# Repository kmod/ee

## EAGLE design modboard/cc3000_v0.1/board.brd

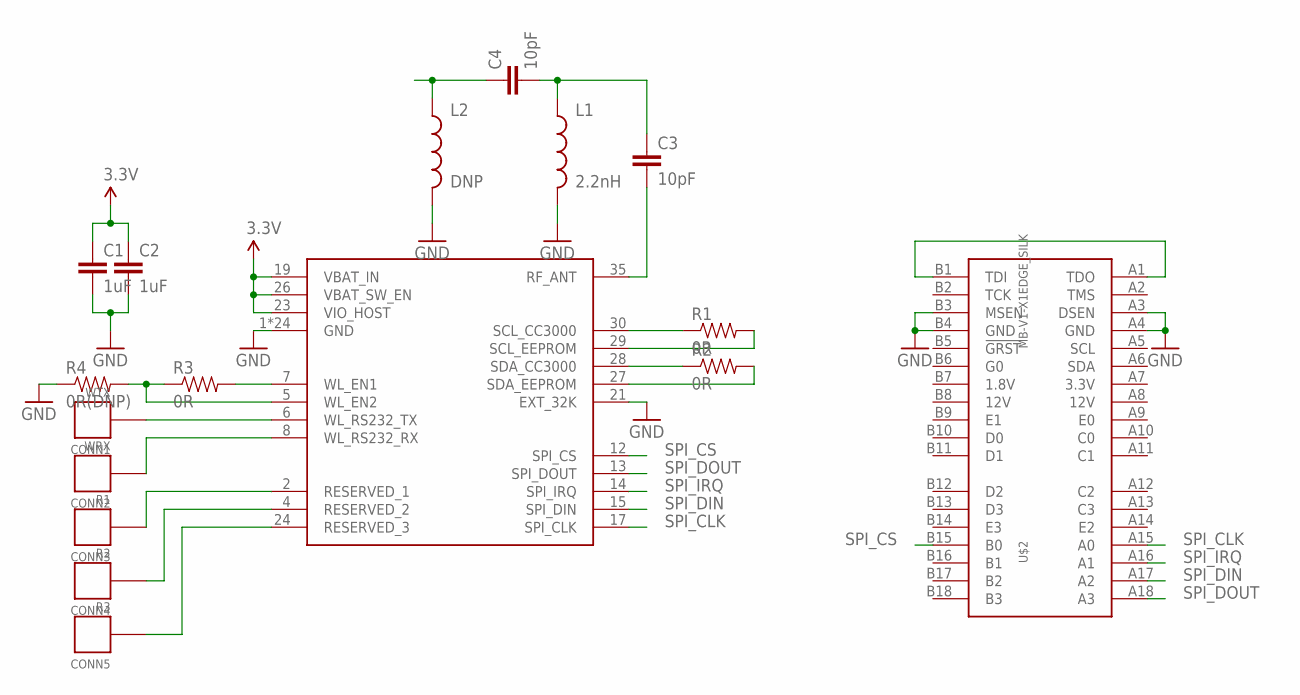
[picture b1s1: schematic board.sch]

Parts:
C1, C2: 1uF; 0603-CAP
C3, C4: 10pF; 0402-CAP
CONN1: WTX; HOLE_22AWG
CONN2: WRX; HOLE_22AWG
CONN3: R1; HOLE_22AWG
CONN4: R2; HOLE_22AWG
CONN5: R3; HOLE_22AWG
L1: 2.2nH; 0603
L2: DNP; 0603
R1, R2, R3: 0R; 0603-RES
R4: 0R(DNP); 0603-RES
U$1: CC3000
U$2: MB-V1-X1EDGE_SILK; MB-V1-X1-EDGE

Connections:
3.3V: C1.1, C2.1, U$1.19 (VBAT_IN), U$1.23 (VIO_HOST), U$1.26 (VBAT_SW_EN)
GND: C1.2, C2.2, L1.2, L2.2, R4.1, U$1.1 (GND), U$1.9 (GND), U$1.10 (GND), U$1.11 (GND), U$1.16 (GND), U$1.18 (GND), U$1.20 (GND), U$1.21 (EXT_32K), U$1.22 (GND), U$1.25 (GND), U$1.31 (GND), U$1.32 (GND), U$1.33 (GND), U$1.34 (GND), U$1.36 (GND), U$1.37 (GND), U$1.38 (GND), U$1.39 (GND), U$1.40 (GND), U$1.41 (GND), U$1.42 (GND), U$1.43 (GND), U$1.44 (GND), U$1.45 (GND), U$1.46 (GND), U$2.A3 (DSEN), U$2.A4 (GND), U$2.B3 (MSEN), U$2.B4 (GND)
unnamed: R1.1, U$1.30 (SCL_CC3000)
unnamed: R1.2, U$1.29 (SCL_EEPROM)
unnamed: R2.1, U$1.28 (SDA_CC3000)
unnamed: R2.2, U$1.27 (SDA_EEPROM)
unnamed: R3.2, U$1.7 (WL_EN1)
unnamed: R3.1, R4.2, U$1.5 (WL_EN2)
unnamed: CONN1.P, U$1.6 (WL_RS232_TX)
unnamed: CONN2.P, U$1.8 (WL_RS232_RX)
unnamed: CONN3.P, U$1.2 (RESERVED_1)
unnamed: CONN4.P, U$1.4 (RESERVED_2)
unnamed: CONN5.P, U$1.24 (RESERVED_3)
unnamed: C3.2, U$1.35 (RF_ANT)
unnamed: C3.1, C4.2, L1.1
unnamed: U$2.A1 (TDO), U$2.B1 (TDI)
unnamed: C4.1, L2.1
SPI_CLK: U$1.17 (SPI_CLK), U$2.A15 (A0)
SPI_CS: U$1.12 (SPI_CS), U$2.B15 (B0)
SPI_DIN: U$1.15 (SPI_DIN), U$2.A17 (A2)
SPI_DOUT: U$1.13 (SPI_DOUT), U$2.A18 (A3)
SPI_IRQ: U$1.14 (SPI_IRQ), U$2.A16 (A1)

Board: 2 copper layers, 17 parts (0 on the bottom side), 22 nets, no tracks yet.

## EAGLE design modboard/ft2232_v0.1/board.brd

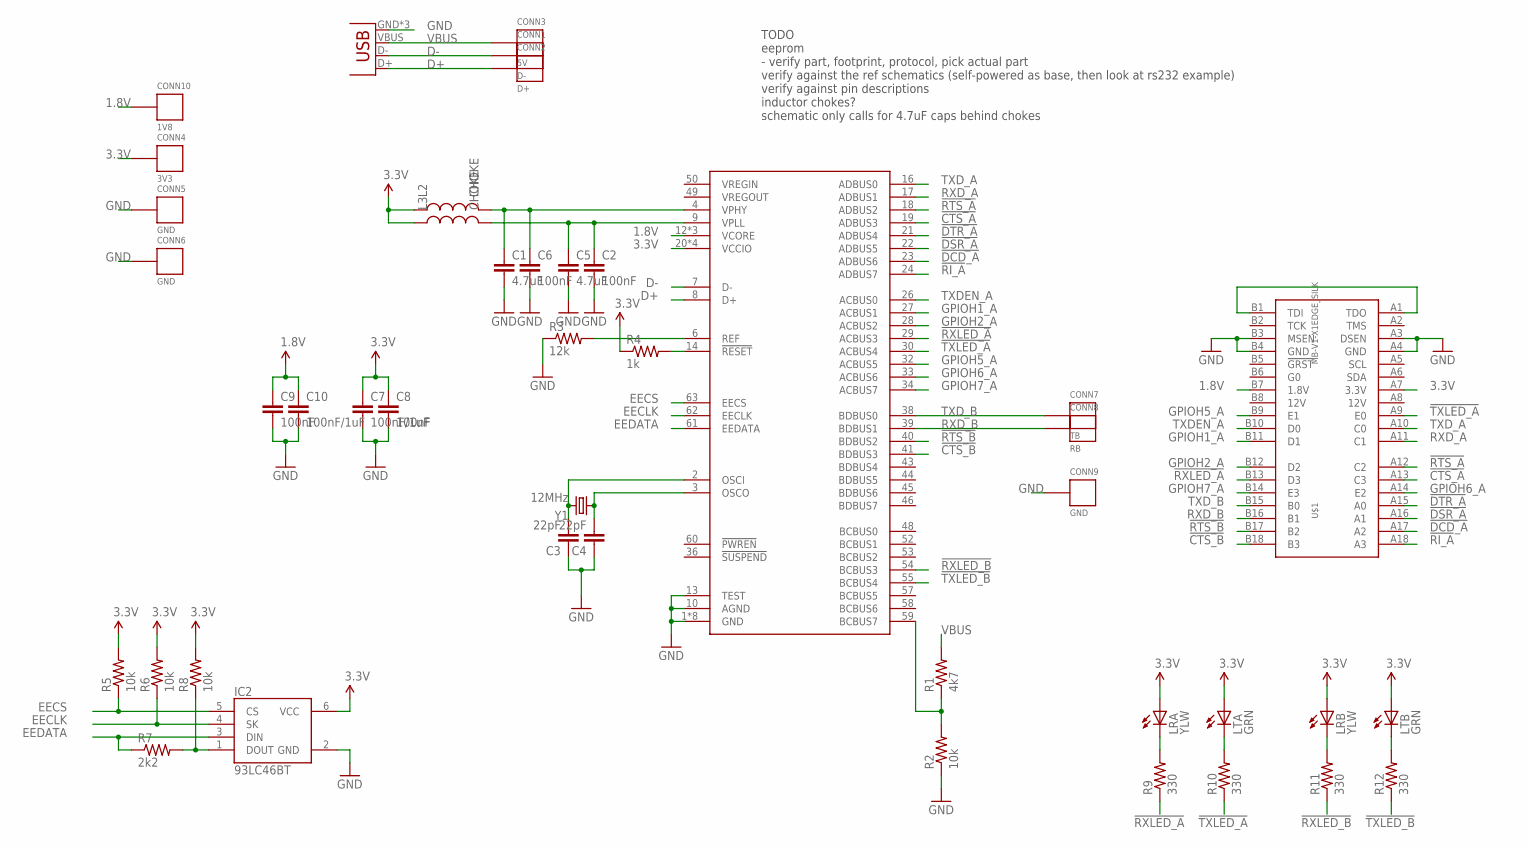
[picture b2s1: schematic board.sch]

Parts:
C1, C5: 4.7uF; 0805
C2, C6, C8, C9: 100nF; 0402-CAP
C3, C4: 22pF; 0402-CAP
C7, C10: 100nF/1uF; 0402-CAP
CONN1: D-; TESTPAD-1.27
CONN2: D+; TESTPAD-1.27
CONN3: 5V; TESTPAD-1.27
CONN4: 3V3; HOLE_22AWG
CONN5, CONN9: GND; HOLE_22AWG
CONN6: GND; CLIP-AREA
CONN7: TB; HOLE_22AWG
CONN8: RB; HOLE_22AWG
CONN10: 1V8; HOLE_22AWG
IC1: FT2232HL; TQFP64_LONGPAD
IC2: 93LC46BT; SOT23-6L
JP2: USBMICROB; USB-MICROB
L2, L3: CHOKE; 0603
LRA: YLW; 0603_LED
LRB: YLW; 0603_LED
LTA: GRN; 0603_LED
LTB: GRN; 0603_LED
R1: 4k7; 0603-RES
R2, R5, R6, R8: 10k; 0603-RES
R3: 12k; 0603-RES
R4: 1k; 0603-RES
R7: 2k2; 0603-RES
R9, R10, R11, R12: 330; 0603-RES
U$1: MB-V1-X1EDGE_SILK; MB-V1-X1-EDGE
Y1: 12MHz; HC49US

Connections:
1.8V: C9.1, C10.1, CONN10.P, IC1.12 (VCORE), IC1.37 (VCORE), IC1.64 (VCORE), U$1.B7 (1.8V)
3.3V: C7.1, C8.1, CONN4.P, IC1.20 (VCCIO), IC1.31 (VCCIO), IC1.42 (VCCIO), IC1.56 (VCCIO), IC2.6 (VCC), L2.1, L3.1, LRA.A, LRB.A, LTA.A, LTB.A, R4.1, R5.2, R6.2, R8.2, U$1.A7 (3.3V)
!CTS_A: IC1.19 (ADBUS3), U$1.A13 (C3)
!CTS_B: IC1.41 (BDBUS3), U$1.B18 (B3)
!DCD_A: IC1.23 (ADBUS6), U$1.A17 (A2)
!DSR_A: IC1.22 (ADBUS5), U$1.A16 (A1)
!DTR_A: IC1.21 (ADBUS4), U$1.A15 (A0)
!RI_A: IC1.24 (ADBUS7), U$1.A18 (A3)
!RTS_A: IC1.18 (ADBUS2), U$1.A12 (C2)
!RTS_B: IC1.40 (BDBUS2), U$1.B17 (B2)
!RXLED_A: IC1.29 (ACBUS3), R9.1, U$1.B13 (D3)
!RXLED_B: IC1.54 (BCBUS3), R11.1
!TXLED_A: IC1.30 (ACBUS4), R10.1, U$1.A9 (E0)
!TXLED_B: IC1.55 (BCBUS4), R12.1
D+: CONN2.P, IC1.8 (D+), JP2.D+
D-: CONN1.P, IC1.7 (D-), JP2.D-
EECLK: IC1.62 (EECLK), IC2.4 (SK), R6.1
EECS: IC1.63 (EECS), IC2.5 (CS), R5.1
EEDATA: IC1.61 (EEDATA), IC2.3 (DIN), R7.1
GND: C1.2, C2.2, C3.1, C4.1, C5.2, C6.2, C7.2, C8.2, C9.2, C10.2, CONN5.P, CONN6.P$1, CONN6.P$2, CONN9.P, IC1.1 (GND), IC1.5 (GND), IC1.10 (AGND), IC1.11 (GND), IC1.13 (TEST), IC1.15 (GND), IC1.25 (GND), IC1.35 (GND), IC1.47 (GND), IC1.51 (GND), IC2.2 (GND), JP2.GND, JP2.MT1 (GND), JP2.MT2 (GND), R2.1, R3.1, U$1.A3 (DSEN), U$1.A4 (GND), U$1.B3 (MSEN), U$1.B4 (GND)
GPIOH1_A: IC1.27 (ACBUS1), U$1.B11 (D1)
GPIOH2_A: IC1.28 (ACBUS2), U$1.B12 (D2)
GPIOH5_A: IC1.32 (ACBUS5), U$1.B9 (E1)
GPIOH6_A: IC1.33 (ACBUS6), U$1.A14 (E2)
GPIOH7_A: IC1.34 (ACBUS7), U$1.B14 (E3)
unnamed: C3.2, IC1.2 (OSCI), Y1.2
unnamed: C4.2, IC1.3 (OSCO), Y1.1
unnamed: IC1.59 (BCBUS7), R1.1, R2.2
unnamed: IC1.6 (REF), R3.2
unnamed: C1.1, C6.1, IC1.4 (VPHY), L2.2
unnamed: IC1.14 (!RESET), R4.2
unnamed: C2.1, C5.1, IC1.9 (VPLL), L3.2
unnamed: IC2.1 (DOUT), R7.2, R8.1
unnamed: LRA.C, R9.2
unnamed: LTA.C, R10.2
unnamed: LRB.C, R11.2
unnamed: LTB.C, R12.2
unnamed: U$1.A1 (TDO), U$1.B1 (TDI)
RXD_A: IC1.17 (ADBUS1), U$1.A11 (C1)
RXD_B: CONN8.P, IC1.39 (BDBUS1), U$1.B16 (B1)
TXDEN_A: IC1.26 (ACBUS0), U$1.B10 (D0)
TXD_A: IC1.16 (ADBUS0), U$1.A10 (C0)
TXD_B: CONN7.P, IC1.38 (BDBUS0), U$1.B15 (B0)
VBUS: CONN3.P, JP2.VBUS, R1.2

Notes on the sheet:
TODO eeprom - verify part, footprint, protocol, pick actual part verify against the ref schematics (self-powered as base, then look at rs232 example) verify against pin descriptions inductor chokes? schematic only calls for 4.7uF caps behind chokes

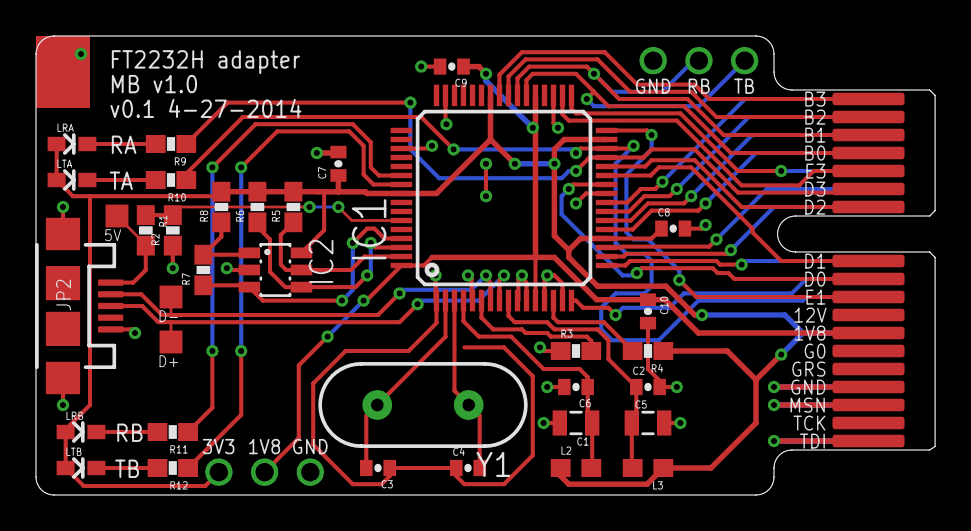
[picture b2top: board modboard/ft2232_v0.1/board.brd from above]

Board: 2 copper layers, 50.0 x 25.5 mm, 43 parts (0 on the bottom side), 44 nets.

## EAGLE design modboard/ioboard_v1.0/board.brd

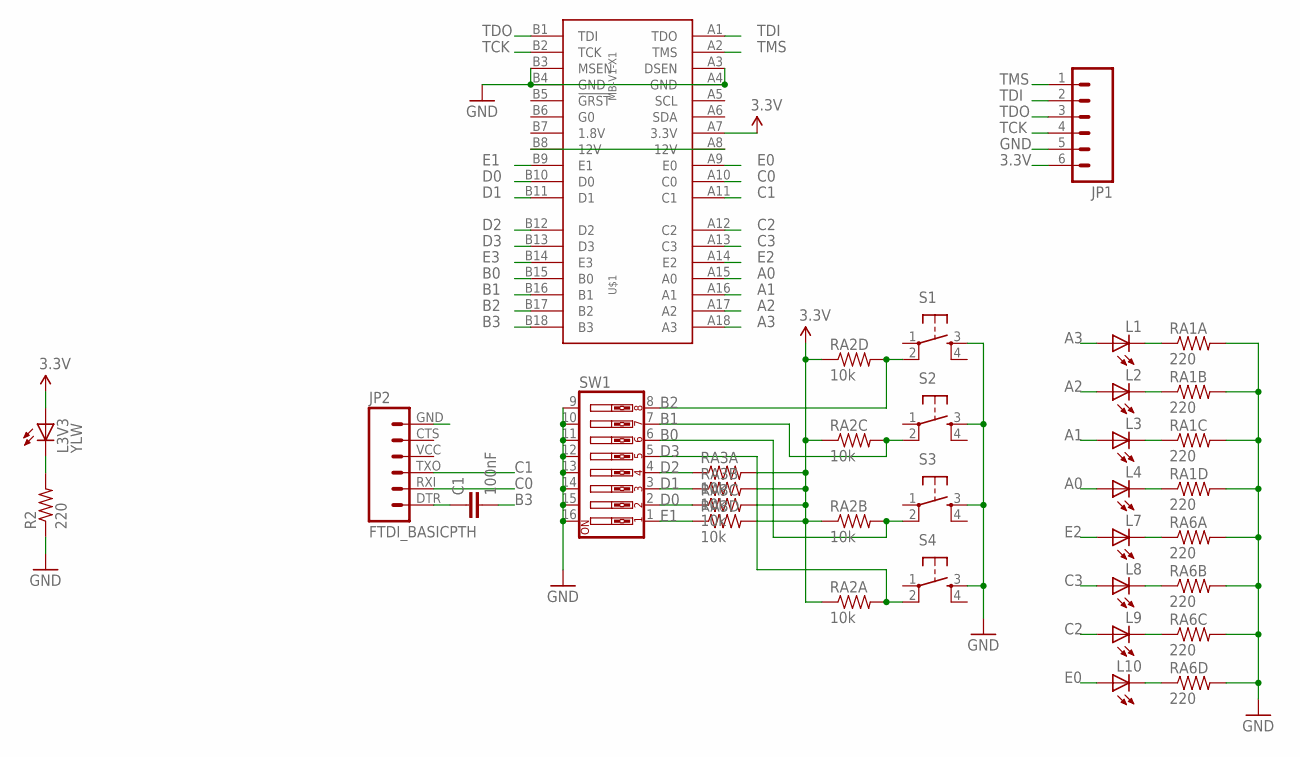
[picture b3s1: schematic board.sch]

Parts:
C1: 100nF; 0402-CAP
JP1: M06LOCK; 1X06_LOCK
JP2: FTDI_BASICPTH; FTDI_BASIC
L1, L2, L3, L4, L7, L8, L9, L10: LED0603; 0603_LED
L3V3: YLW; 0603_LED
R2: 220; 0603-RES
RA1, RA6: 220; 0603-ARV
RA2, RA3: 10k; 0603-ARV
S1, S2, S3, S4: TAC_SWITCHPTH; TACTILE-PTH
SW1: SW_DIP-8; DIPSWITCH-08
U$1: MB-V1-X1; PCIE-X1-EDGE

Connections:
3.3V: JP1.6, L3V3.A, RA2.1, RA2.2 (1), RA2.3 (1), RA2.4 (1), RA3.5 (2), RA3.6 (2), RA3.7 (2), RA3.8 (2), U$1.A7 (3.3V)
A0: L4.A, U$1.A15 (A0)
A1: L3.A, U$1.A16 (A1)
A2: L2.A, U$1.A17 (A2)
A3: L1.A, U$1.A18 (A3)
B0: RA2.7 (2), S3.2, SW1.6, U$1.B15 (B0)
B1: RA2.6 (2), S2.2, SW1.7, U$1.B16 (B1)
B2: RA2.5 (2), S1.2, SW1.8, U$1.B17 (B2)
B3: C1.2, U$1.B18 (B3)
C0: JP2.RXI (2), U$1.A10 (C0)
C1: JP2.TXO (3), U$1.A11 (C1)
C2: L9.A, U$1.A12 (C2)
C3: L8.A, U$1.A13 (C3)
D0: RA3.3 (1), SW1.2, U$1.B10 (D0)
D1: RA3.2 (1), SW1.3, U$1.B11 (D1)
D2: RA3.1, SW1.4, U$1.B12 (D2)
D3: RA2.8 (2), S4.2, SW1.5, U$1.B13 (D3)
E0: L10.A, U$1.A9 (E0)
E1: RA3.4 (1), SW1.1, U$1.B9 (E1)
E2: L7.A, U$1.A14 (E2)
E3: U$1.B14 (E3)
GND: JP1.5, JP2.GND (6), R2.1, RA1.5 (2), RA1.6 (2), RA1.7 (2), RA1.8 (2), RA6.5 (2), RA6.6 (2), RA6.7 (2), RA6.8 (2), S1.3, S2.3, S3.3, S4.3, SW1.9, SW1.10, SW1.11, SW1.12, SW1.13, SW1.14, SW1.15, SW1.16, U$1.A3 (DSEN), U$1.A4 (GND), U$1.B3 (MSEN), U$1.B4 (GND)
unnamed: L1.C, RA1.1
unnamed: L2.C, RA1.2 (1)
unnamed: L3.C, RA1.3 (1)
unnamed: L4.C, RA1.4 (1)
unnamed: L3V3.C, R2.2
unnamed: C1.1, JP2.DTR (1)
unnamed: L7.C, RA6.1
unnamed: L8.C, RA6.2 (1)
unnamed: L9.C, RA6.3 (1)
unnamed: L10.C, RA6.4 (1)
unnamed: U$1.A8 (12V), U$1.B8 (12V)
TCK: JP1.4, U$1.B2 (TCK)
TDI: JP1.2, U$1.A1 (TDO)
TDO: JP1.3, U$1.B1 (TDI)
TMS: JP1.1, U$1.A2 (TMS)

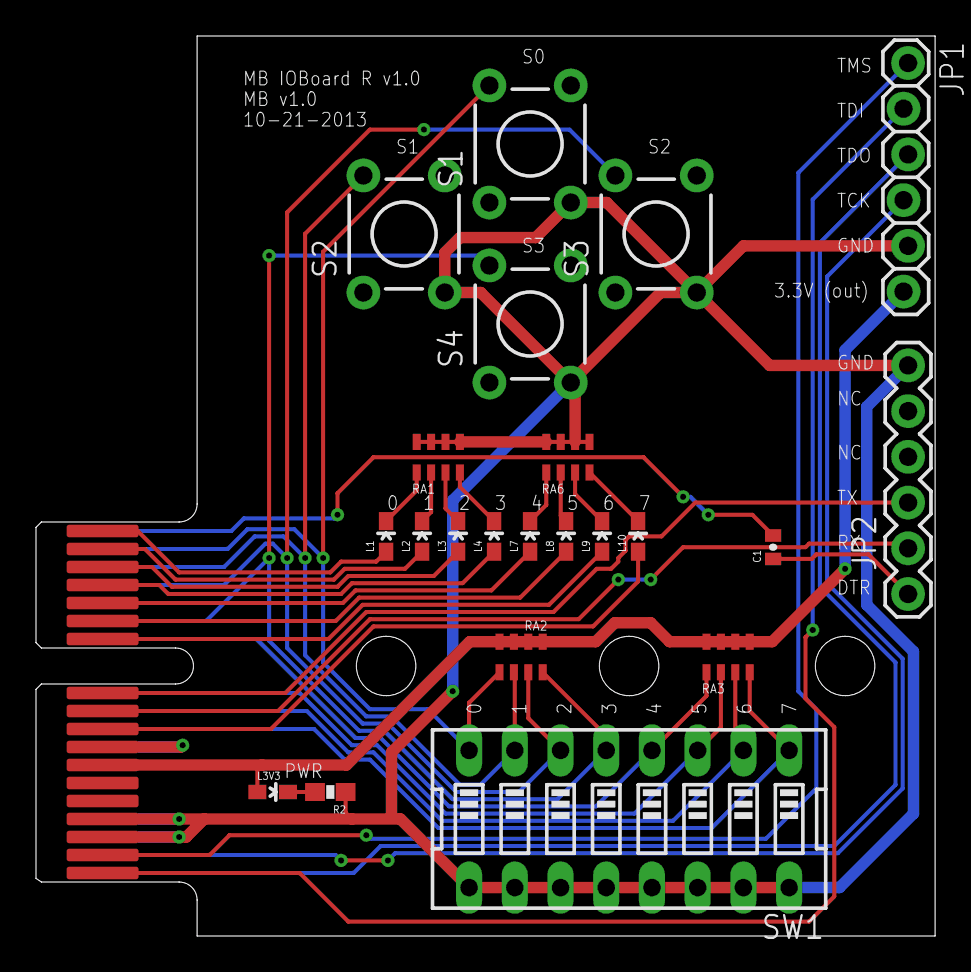
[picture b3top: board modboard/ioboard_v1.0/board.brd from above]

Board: 2 copper layers, 50.0 x 50.0 mm, 23 parts (1 on the bottom side), 36 nets.

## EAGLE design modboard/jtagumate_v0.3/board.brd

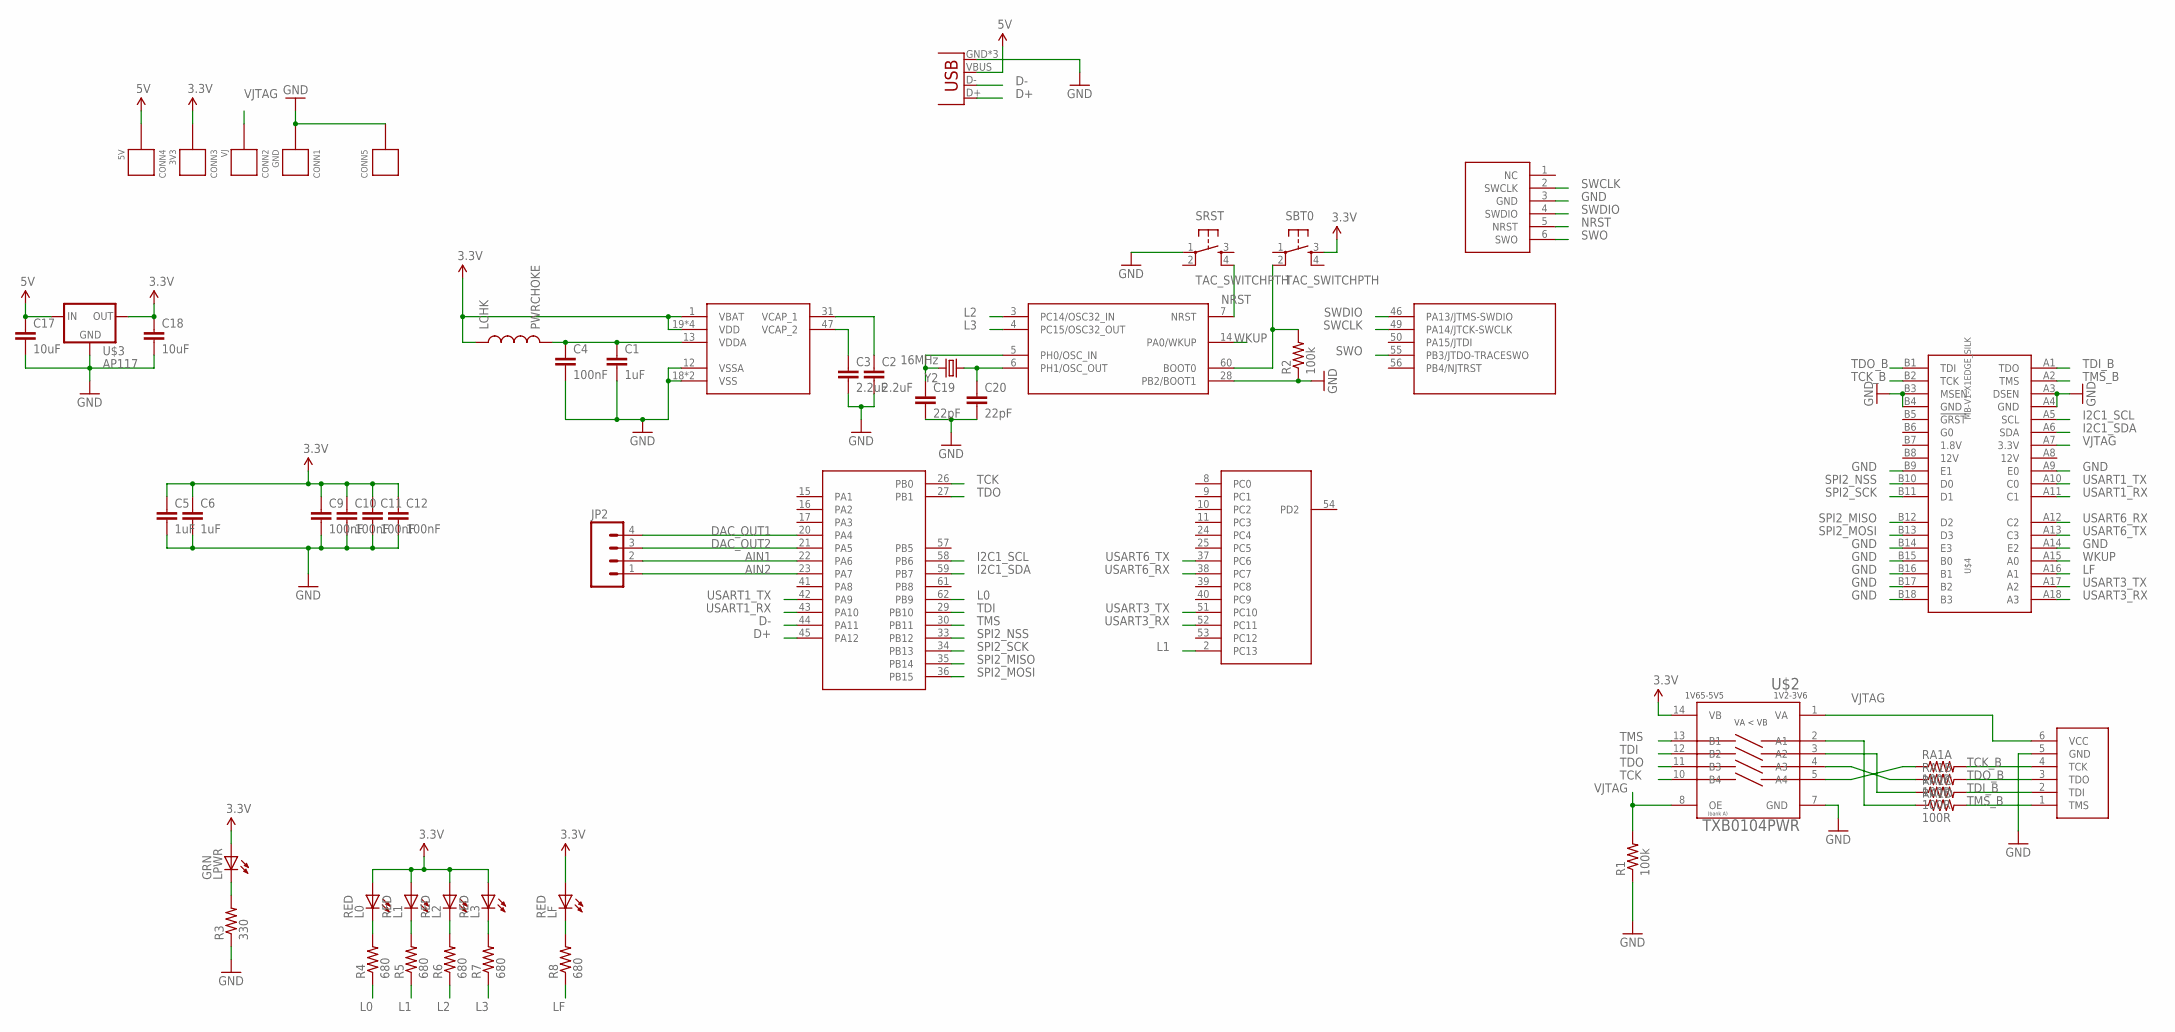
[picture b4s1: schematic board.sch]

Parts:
C1, C5, C6: 1uF; 0603-CAP
C2, C3: 2.2uF; 0603-CAP
C4, C9, C10, C11, C12: 100nF; 0402-CAP
C17, C18: 10uF; 0805
C19, C20: 22pF; 0402-CAP
CONN1: GND; HOLE_22AWG
CONN2: VJ; HOLE_22AWG
CONN3: 3V3; HOLE_22AWG
CONN4: 5V; HOLE_22AWG
CONN5: CONNECTORCLIP; CLIP-AREA
JP1: USB-MICROB
JP2: M04PTH; 1X04
L0, L1, L2, L3: RED; 0603_LED
LCHK: PWRCHOKE; 0603
LF: RED; 0603_LED
LPWR: GRN; 0603_LED
R1, R2: 100k; 0603-RES
R3: 330; 0603-RES
R4, R5, R6, R7, R8: 680; 0603-RES
RA1: 100R; 0603-ARV
SBT0: TAC_SWITCHPTH; TACTILE-PTH
SRST: TAC_SWITCHPTH; TACTILE-PTH
U$1: STM32F407R; TQFP64_LONGPAD
U$2: TXB0104PWR; TSSOP14
U$3: AP117; SOT223
U$4: MB-V1-X1EDGE_SILK; MB-V1-X1-EDGE
U$5: JTAGDIGILENT; 1X06
U$6: STLINK; 1X06
Y2: 16MHz; HC49US

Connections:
3.3V: C5.1, C6.1, C9.1, C10.1, C11.1, C12.1, C18.1, CONN3.P, L0.A, L1.A, L2.A, L3.A, LCHK.1, LF.A, LPWR.A, SBT0.3, U$1.1 (VBAT), U$1.19 (VDD), U$1.32 (VDD), U$1.48 (VDD), U$1.64 (VDD), U$2.14 (VB), U$3.2 (OUT), U$3.4 (OUT)
5V: C17.1, CONN4.P, JP1.VBUS, U$3.3 (IN)
AIN1: JP2.2, U$1.22 (PA6)
AIN2: JP2.1, U$1.23 (PA7)
BOOT0: R2.2, SBT0.2, U$1.60 (BOOT0)
D+: JP1.D+, U$1.45 (PA12)
D-: JP1.D-, U$1.44 (PA11)
DAC_OUT1: JP2.4, U$1.20 (PA4)
DAC_OUT2: JP2.3, U$1.21 (PA5)
GND: C1.2, C2.2, C3.2, C4.2, C5.2, C6.2, C9.2, C10.2, C11.2, C12.2, C17.2, C18.2, C19.2, C20.2, CONN1.P, CONN5.P$1, CONN5.P$2, JP1.GND, JP1.MT1 (GND), JP1.MT2 (GND), R1.1, R2.1, R3.1, SRST.1, U$1.12 (VSSA), U$1.18 (VSS), U$1.28 (PB2/BOOT1), U$1.63 (VSS), U$2.7 (GND), U$3.1 (GND), U$4.A3 (DSEN), U$4.A4 (GND), U$4.A9 (E0), U$4.A14 (E2), U$4.B3 (MSEN), U$4.B4 (GND), U$4.B9 (E1), U$4.B14 (E3), U$4.B15 (B0), U$4.B16 (B1), U$4.B17 (B2), U$4.B18 (B3), U$5.5 (GND), U$6.3 (GND)
I2C1_SCL: U$1.58 (PB6), U$4.A5 (SCL)
I2C1_SDA: U$1.59 (PB7), U$4.A6 (SDA)
L0: R4.1, U$1.62 (PB9)
L1: R5.1, U$1.2 (PC13)
L2: R6.1, U$1.3 (PC14/OSC32_IN)
L3: R7.1, U$1.4 (PC15/OSC32_OUT)
LF: R8.1, U$4.A16 (A1)
unnamed: C3.1, U$1.47 (VCAP_2)
unnamed: C2.1, U$1.31 (VCAP_1)
unnamed: C19.1, U$1.5 (PH0/OSC_IN), Y2.2
unnamed: C20.1, U$1.6 (PH1/OSC_OUT), Y2.1
unnamed: LPWR.C, R3.2
unnamed: L0.C, R4.2
unnamed: L1.C, R5.2
unnamed: L2.C, R6.2
unnamed: L3.C, R7.2
unnamed: LF.C, R8.2
NRST: SRST.4, U$1.7 (NRST), U$6.5 (NRST)
SPI2_MISO: U$1.35 (PB14), U$4.B12 (D2)
SPI2_MOSI: U$1.36 (PB15), U$4.B13 (D3)
SPI2_NSS: U$1.33 (PB12), U$4.B10 (D0)
SPI2_SCK: U$1.34 (PB13), U$4.B11 (D1)
SWCLK: U$1.49 (PA14/JTCK-SWCLK), U$6.2 (SWCLK)
SWDIO: U$1.46 (PA13/JTMS-SWDIO), U$6.4 (SWDIO)
SWO: U$1.55 (PB3/JTDO-TRACESWO), U$6.6 (SWO)
TCK: U$1.26 (PB0), U$2.10 (B4)
TCK_B: RA1.8 (2), U$4.B2 (TCK), U$5.4 (TCK)
TCK_O: RA1.1, U$2.5 (A4)
TDI: U$1.29 (PB10), U$2.12 (B2)
TDI_B: RA1.6 (2), U$4.A1 (TDO), U$5.2 (TDI)
TDI_O: RA1.3 (1), U$2.3 (A2)
TDO: U$1.27 (PB1), U$2.11 (B3)
TDO_B: RA1.7 (2), U$4.B1 (TDI), U$5.3 (TDO)
TDO_O: RA1.2 (1), U$2.4 (A3)
TMS: U$1.30 (PB11), U$2.13 (B1)
TMS_B: RA1.5 (2), U$4.A2 (TMS), U$5.1 (TMS)
TMS_O: RA1.4 (1), U$2.2 (A1)
USART1_RX: U$1.43 (PA10), U$4.A11 (C1)
USART1_TX: U$1.42 (PA9), U$4.A10 (C0)
USART3_RX: U$1.52 (PC11), U$4.A18 (A3)
USART3_TX: U$1.51 (PC10), U$4.A17 (A2)
USART6_RX: U$1.38 (PC7), U$4.A12 (C2)
USART6_TX: U$1.37 (PC6), U$4.A13 (C3)
VDDA: C1.1, C4.1, LCHK.2, U$1.13 (VDDA)
VJTAG: CONN2.P, R1.2, U$2.1 (VA), U$2.8 (OE), U$4.A7 (3.3V), U$5.6 (VCC)
WKUP: U$1.14 (PA0/WKUP), U$4.A15 (A0)

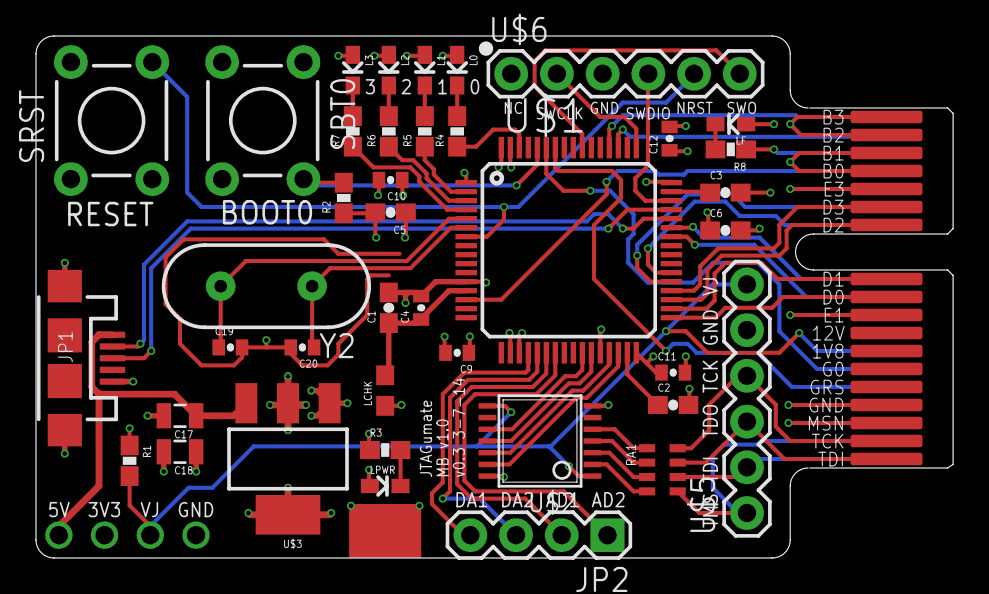
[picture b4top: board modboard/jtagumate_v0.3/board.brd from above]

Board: 4 copper layers, 51.0 x 29.0 mm, 46 parts (1 on the bottom side), 56 nets.

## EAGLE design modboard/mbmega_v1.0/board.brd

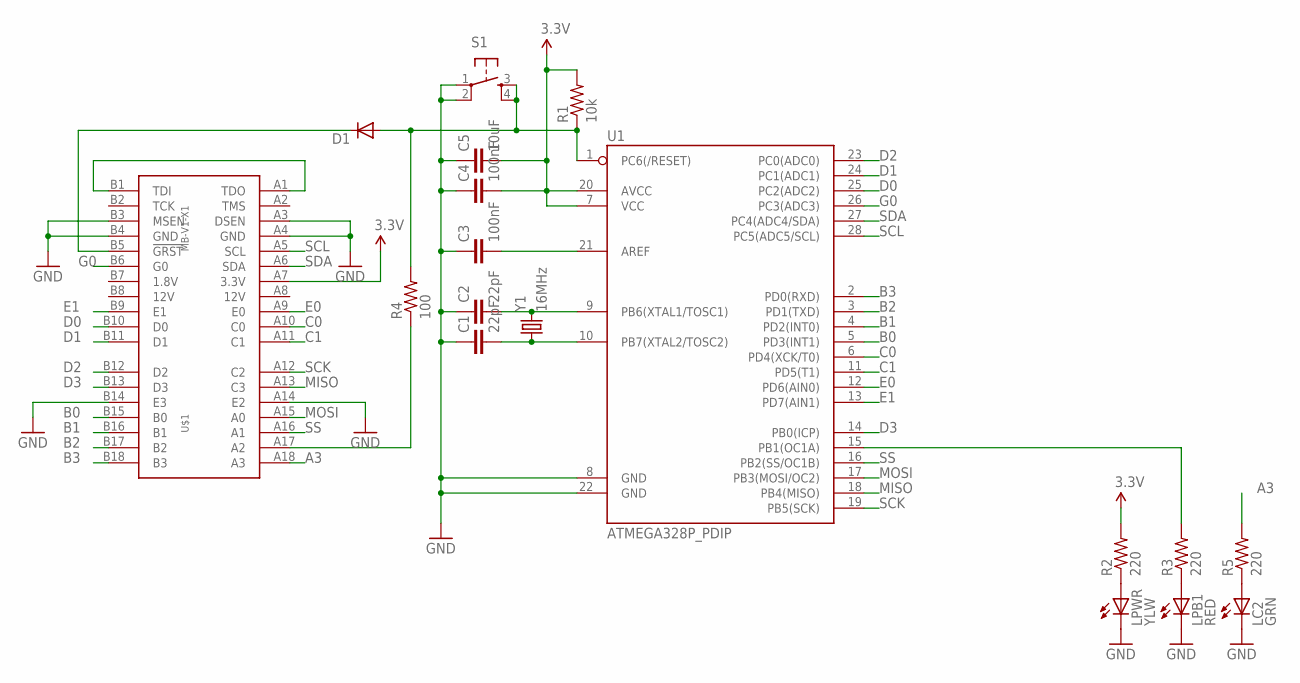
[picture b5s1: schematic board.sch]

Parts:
C1, C2: 22pF; 0402-CAP
C3, C4: 100nF; 0402-CAP
C5: 10uF; 0805
D1: DIODE1N4148; DIODE-1N4148
LC2: GRN; LED-0603
LPB1: RED; LED-0603
LPWR: YLW; LED-0603
R1: 10k; 0603-RES
R2, R3, R5: 220; 0603-RES
R4: 100; 0603-RES
S1: TAC_SWITCHPTH; TACTILE-PTH
U1: ATMEGA328P_PDIP; DIL28-3
U$1: MB-V1-X1; PCIE-X1-EDGE
Y1: 16MHz; HC49US

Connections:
3.3V: C4.2, C5.2, R1.2, R2.2, U1.7 (VCC), U1.20 (AVCC), U$1.A7 (3.3V)
A3: R5.2, U$1.A18 (A3)
B0: U1.5 (PD3(INT1)), U$1.B15 (B0)
B1: U1.4 (PD2(INT0)), U$1.B16 (B1)
B2: U1.3 (PD1(TXD)), U$1.B17 (B2)
B3: U1.2 (PD0(RXD)), U$1.B18 (B3)
C0: U1.6 (PD4(XCK/T0)), U$1.A10 (C0)
C1: U1.11 (PD5(T1)), U$1.A11 (C1)
D0: U1.25 (PC2(ADC2)), U$1.B10 (D0)
D1: U1.24 (PC1(ADC1)), U$1.B11 (D1)
D2: U1.23 (PC0(ADC0)), U$1.B12 (D2)
D3: U1.14 (PB0(ICP)), U$1.B13 (D3)
E0: U1.12 (PD6(AIN0)), U$1.A9 (E0)
E1: U1.13 (PD7(AIN1)), U$1.B9 (E1)
G0: U1.26 (PC3(ADC3)), U$1.B6 (G0)
GND: C1.1, C2.1, C3.1, C4.1, C5.1, LC2.C, LPB1.C, LPWR.C, S1.1, S1.2, U1.8 (GND), U1.22 (GND), U$1.A3 (DSEN), U$1.A4 (GND), U$1.A14 (E2), U$1.B3 (MSEN), U$1.B4 (GND), U$1.B14 (E3)
MISO: U1.18 (PB4(MISO)), U$1.A13 (C3)
MOSI: U1.17 (PB3(MOSI/OC2)), U$1.A15 (A0)
unnamed: D1.C, U$1.B5 (!GRST)
unnamed: LPB1.A, R3.1
unnamed: C2.2, U1.9 (PB6(XTAL1/TOSC1)), Y1.2
unnamed: C1.2, U1.10 (PB7(XTAL2/TOSC2)), Y1.1
unnamed: C3.2, U1.21 (AREF)
unnamed: U$1.A1 (TDO), U$1.B1 (TDI)
unnamed: LC2.A, R5.1
unnamed: R3.2, U1.15 (PB1(OC1A))
unnamed: R4.1, U$1.A17 (A2)
unnamed: LPWR.A, R2.1
RST: D1.A, R1.1, R4.2, S1.3, S1.4, U1.1 (PC6(/RESET))
SCK: U1.19 (PB5(SCK)), U$1.A12 (C2)
SCL: U1.28 (PC5(ADC5/SCL)), U$1.A5 (SCL)
SDA: U1.27 (PC4(ADC4/SDA)), U$1.A6 (SDA)
SS: U1.16 (PB2(SS/OC1B)), U$1.A16 (A1)

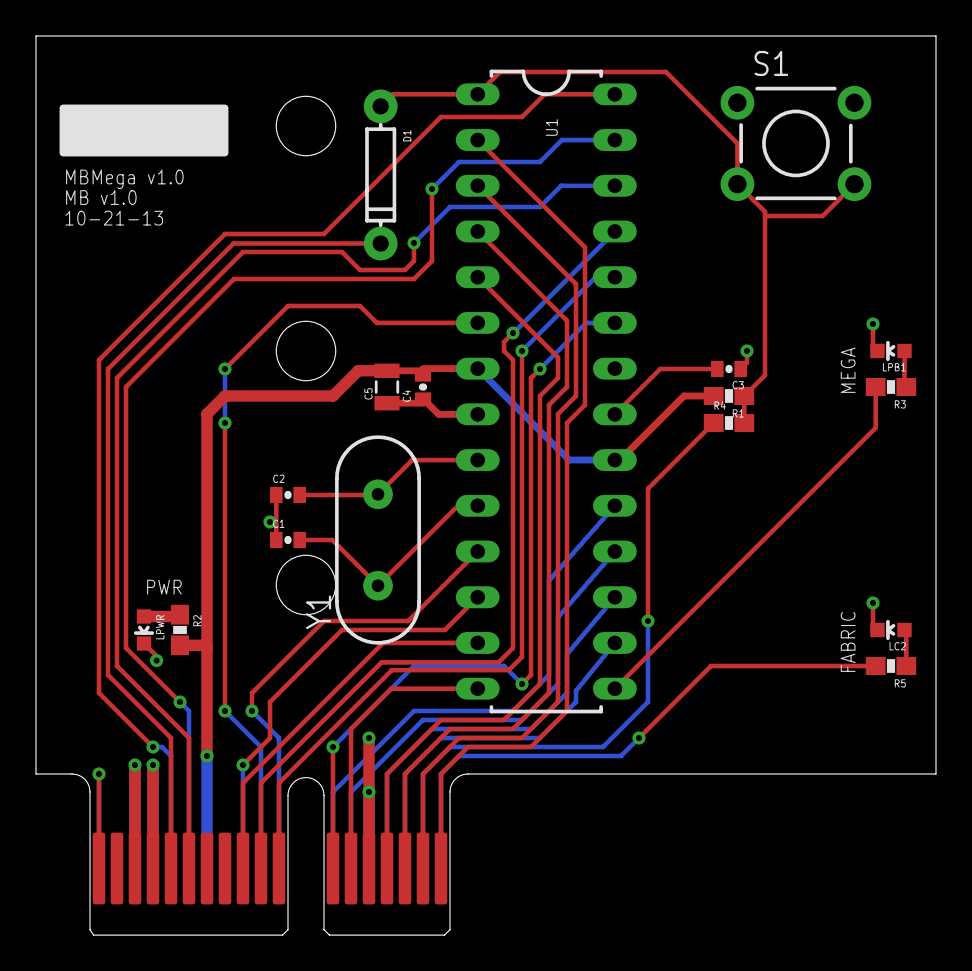
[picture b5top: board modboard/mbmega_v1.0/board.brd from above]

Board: 2 copper layers, 50.0 x 50.0 mm, 18 parts (0 on the bottom side), 33 nets.

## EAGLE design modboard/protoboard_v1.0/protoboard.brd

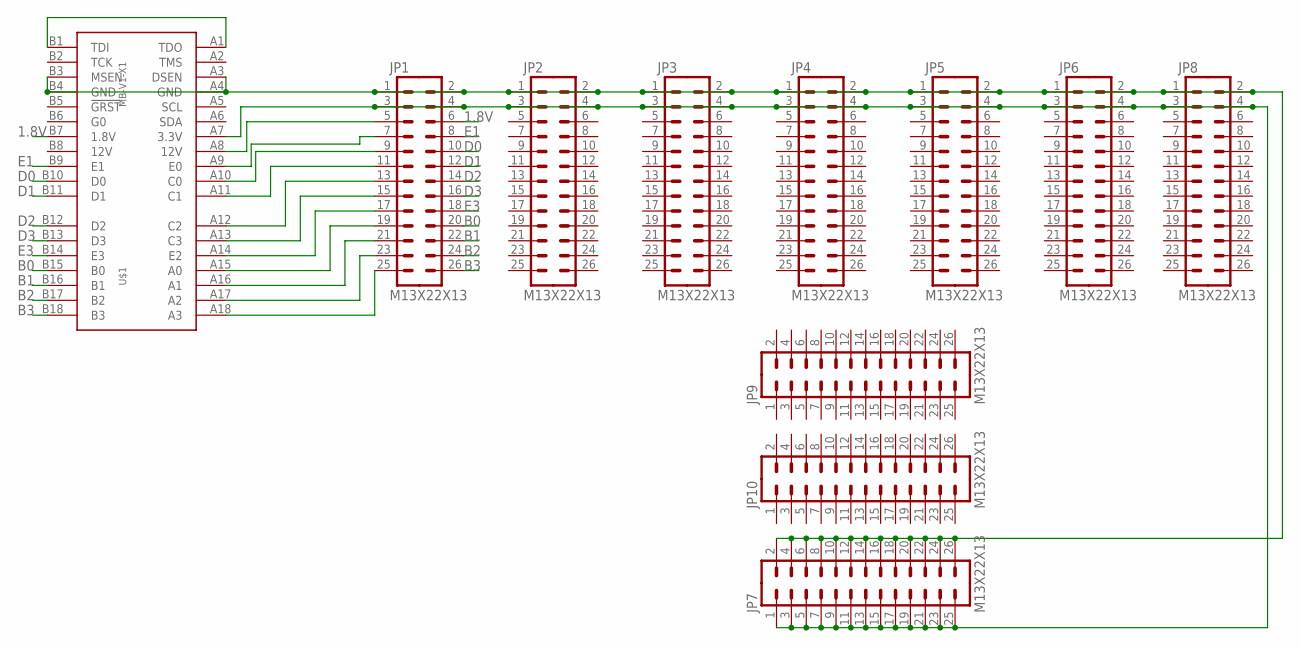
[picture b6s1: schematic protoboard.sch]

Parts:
JP1, JP2, JP3, JP4, JP5, JP6, JP7, JP8, JP9, JP10: M13X22X13; 2X13
U$1: MB-V1-X1; PCIE-X1-EDGE

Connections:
1.8V: JP1.6, U$1.B7 (1.8V)
3.3V: JP1.3, JP1.4, JP2.3, JP2.4, JP3.3, JP3.4, JP4.3, JP4.4, JP5.3, JP5.4, JP6.3, JP6.4, JP7.1, JP7.3, JP7.5, JP7.7, JP7.9, JP7.11, JP7.13, JP7.15, JP7.17, JP7.19, JP7.21, JP7.23, JP7.25, JP8.3, JP8.4, U$1.A7 (3.3V)
B0: JP1.20, U$1.B15 (B0)
B1: JP1.22, U$1.B16 (B1)
B2: JP1.24, U$1.B17 (B2)
B3: JP1.26, U$1.B18 (B3)
D0: JP1.10, U$1.B10 (D0)
D1: JP1.12, U$1.B11 (D1)
D2: JP1.14, U$1.B12 (D2)
D3: JP1.16, U$1.B13 (D3)
E1: JP1.8, U$1.B9 (E1)
E3: JP1.18, U$1.B14 (E3)
GND: JP1.1, JP1.2, JP2.1, JP2.2, JP3.1, JP3.2, JP4.1, JP4.2, JP5.1, JP5.2, JP6.1, JP6.2, JP7.2, JP7.4, JP7.6, JP7.8, JP7.10, JP7.12, JP7.14, JP7.16, JP7.18, JP7.20, JP7.22, JP7.24, JP7.26, JP8.1, JP8.2, U$1.A3 (DSEN), U$1.A4 (GND), U$1.B3 (MSEN), U$1.B4 (GND)
unnamed: U$1.A1 (TDO), U$1.B1 (TDI)
unnamed: JP1.5, U$1.A8 (12V)
unnamed: JP1.25, U$1.A18 (A3)
unnamed: JP1.23, U$1.A17 (A2)
unnamed: JP1.21, U$1.A16 (A1)
unnamed: JP1.19, U$1.A15 (A0)
unnamed: JP1.17, U$1.A14 (E2)
unnamed: JP1.15, U$1.A13 (C3)
unnamed: JP1.13, U$1.A12 (C2)
unnamed: JP1.11, U$1.A11 (C1)
unnamed: JP1.9, U$1.A10 (C0)
unnamed: JP1.7, U$1.A9 (E0)

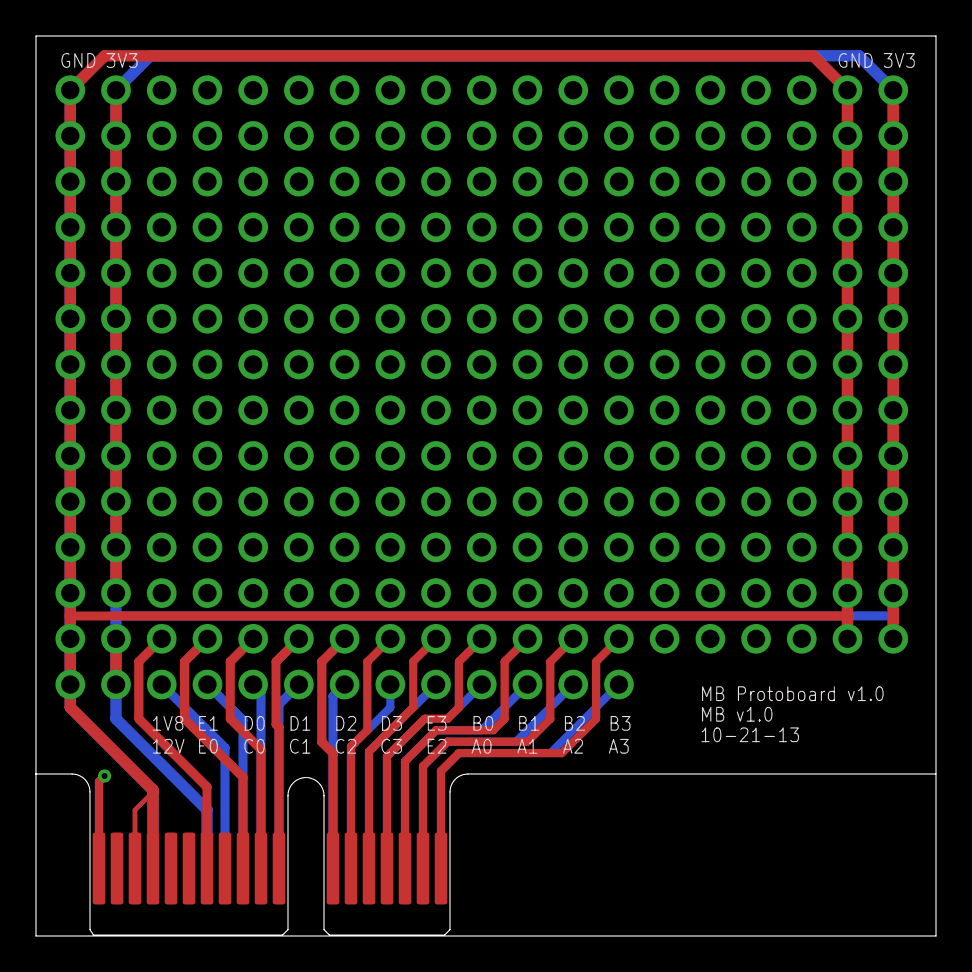
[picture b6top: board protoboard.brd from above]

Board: 2 copper layers, 50.0 x 50.0 mm, 11 parts (0 on the bottom side), 25 nets.

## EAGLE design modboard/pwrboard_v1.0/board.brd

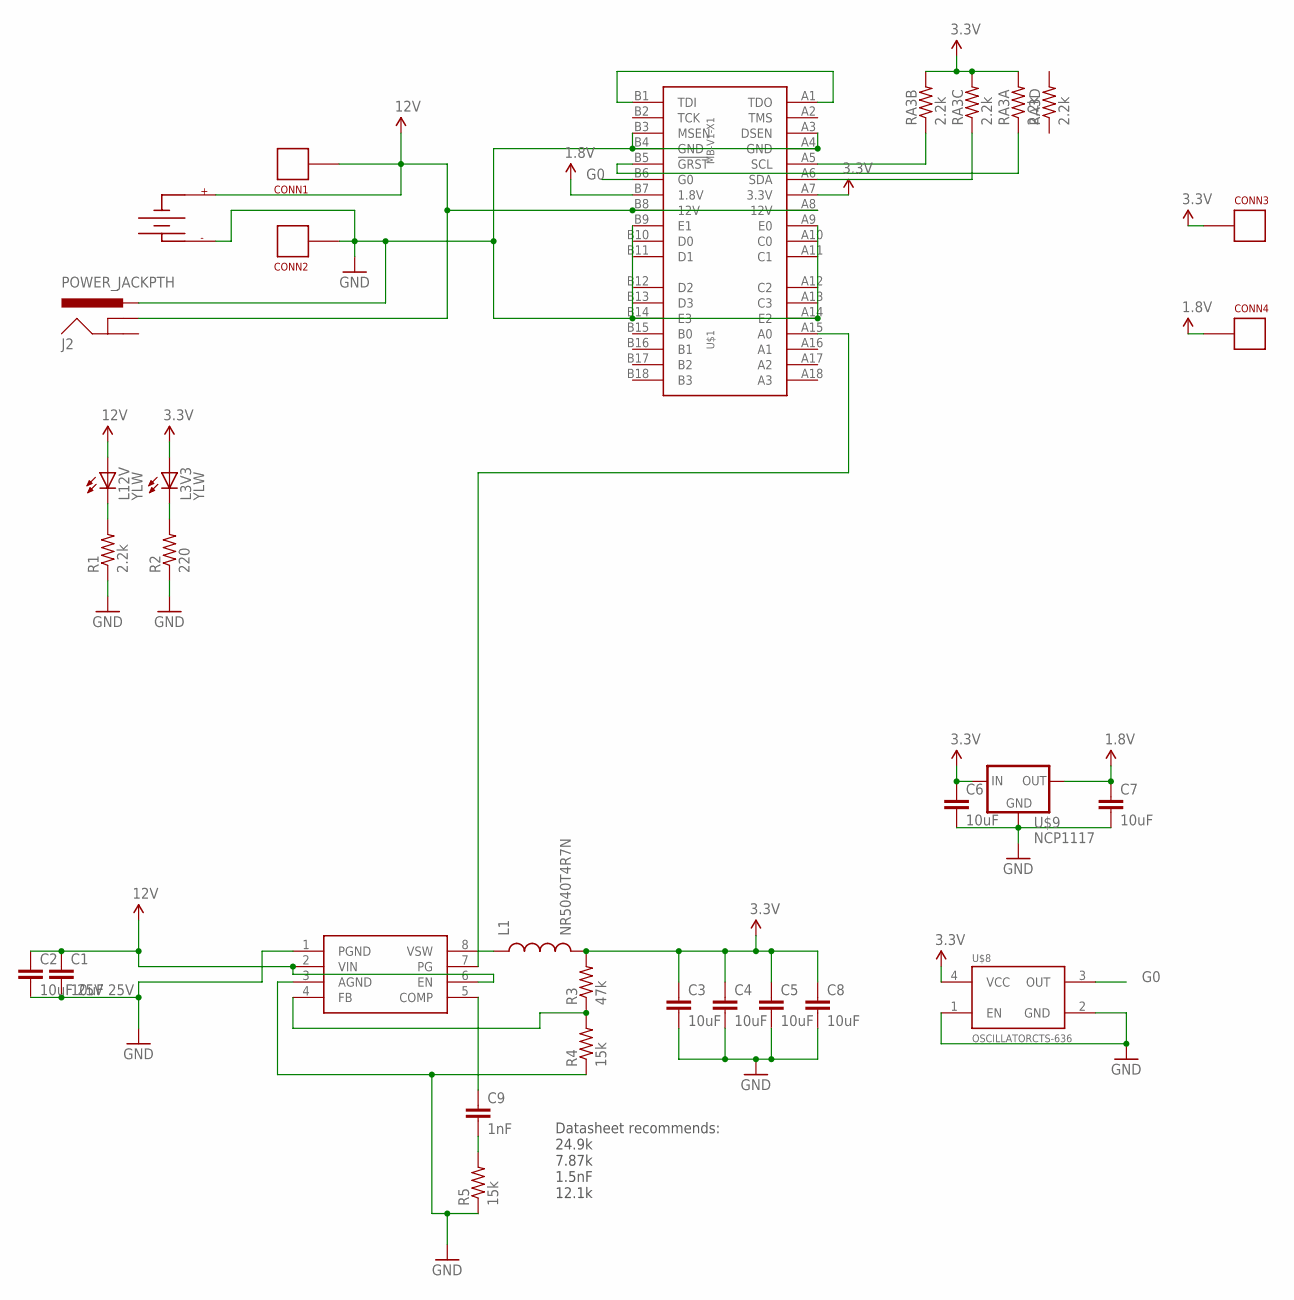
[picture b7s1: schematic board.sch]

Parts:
C1, C2: 10uF 25V; 0805
C3, C4, C5, C6, C7, C8: 10uF; 0805
C9: 1nF; 0402-CAP
CONN1, CONN2, CONN3, CONN4: CONNECTOR18AWG; HOLE_18AWG
J2: POWER_JACKPTH; POWER_JACK_PTH
L1: NR5040T4R7N; NR5040
L3V3, L12V: YLW; 0603_LED
R1: 2.2k; 0603-RES
R2: 220; 0603-RES
R3: 47k; 0603-RES
R4, R5: 15k; 0603-RES
RA3: 2.2k; 0603-ARV
U$1: MB-V1-X1; PCIE-X1-EDGE
U$4: SUPPLYPCIE-6-RA; MOLEX_MINIFITJR_6_RA
U$7: NCP3170; SO08
U$8: OSCILLATORCTS-636; CTS-636
U$9: NCP1117; SOT223

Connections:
1.8V: C7.1, CONN4.P$1, U$1.B7 (1.8V), U$9.2 (OUT), U$9.4 (OUT)
3.3V: C3.1, C4.1, C5.1, C6.1, C8.1, CONN3.P$1, L1.P$2 (2), L3V3.A, R3.2, RA3.6 (2), RA3.7 (2), RA3.8 (2), U$1.A7 (3.3V), U$8.4 (VCC), U$9.3 (IN)
12V: C1.1, C2.1, CONN1.P$1, J2.GNDBREAK, L12V.A, U$1.A8 (12V), U$1.B8 (12V), U$4.1 (VSUPPLY), U$4.3 (VSUPPLY), U$7.2 (VIN), U$7.6 (EN)
G0: U$1.B6 (G0), U$8.3 (OUT)
GND: C1.2, C2.2, C3.2, C4.2, C5.2, C6.2, C7.2, C8.2, CONN2.P$1, J2.PWR, R1.1, R2.1, R4.1, R5.1, U$1.A3 (DSEN), U$1.A4 (GND), U$1.A9 (E0), U$1.A14 (E2), U$1.B3 (MSEN), U$1.B4 (GND), U$1.B9 (E1), U$1.B14 (E3), U$4.4 (GND), U$4.6 (GND), U$7.1 (PGND), U$7.3 (AGND), U$8.1 (EN), U$8.2 (GND), U$9.1 (GND)
unnamed: L12V.C, R1.2
unnamed: L1.P$1 (1), U$7.8 (VSW)
unnamed: U$1.A15 (A0), U$7.7 (PG)
unnamed: R3.1, R4.2, U$7.4 (FB)
unnamed: L3V3.C, R2.2
unnamed: C9.1, U$7.5 (COMP)
unnamed: RA3.3 (1), U$1.A6 (SDA)
unnamed: C9.2, R5.2
unnamed: RA3.2 (1), U$1.A5 (SCL)
unnamed: RA3.1, U$1.B5 (!GRST)
TDI: U$1.A1 (TDO), U$1.B1 (TDI)

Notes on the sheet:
Datasheet recommends: 24.9k 7.87k 1.5nF 12.1k

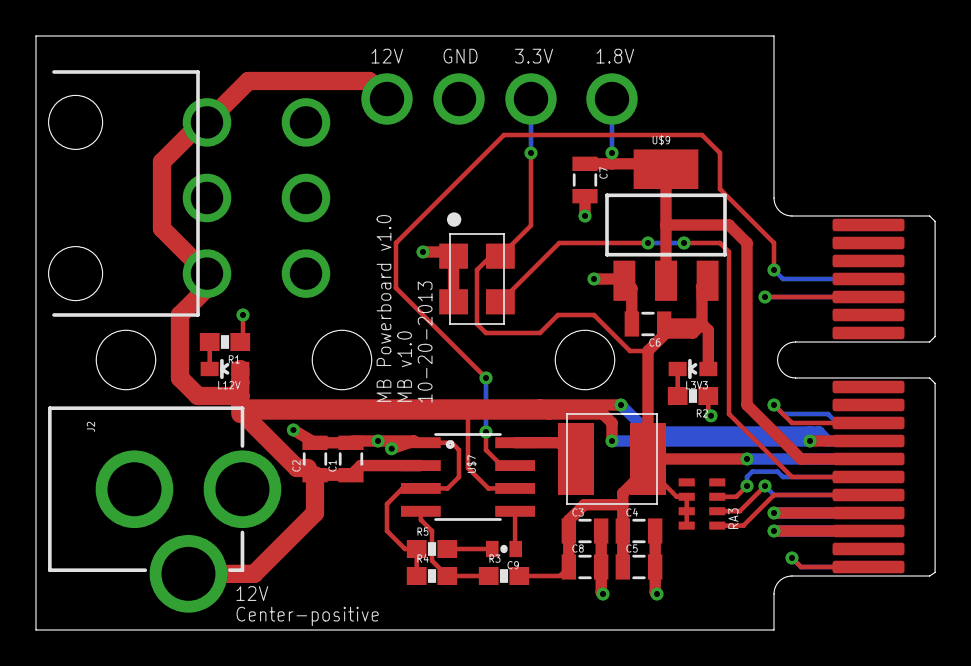
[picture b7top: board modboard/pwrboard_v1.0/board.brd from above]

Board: 2 copper layers, 50.0 x 33.0 mm, 28 parts (0 on the bottom side), 16 nets.

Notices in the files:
parts and their libraries:
SparkFun-DiscreteSemi: Licensing: Creative Commons ShareAlike 4.0 International - https://creativecommons.org/licenses/by-sa/4.0
SparkFun-Aesthetics: Licensing: CC v3.0 Share-Alike You are welcome to use this library for commercial purposes.
